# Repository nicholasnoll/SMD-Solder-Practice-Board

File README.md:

# SMD Solder Practice Board
 A 100x100mm board for SMD soldering practice

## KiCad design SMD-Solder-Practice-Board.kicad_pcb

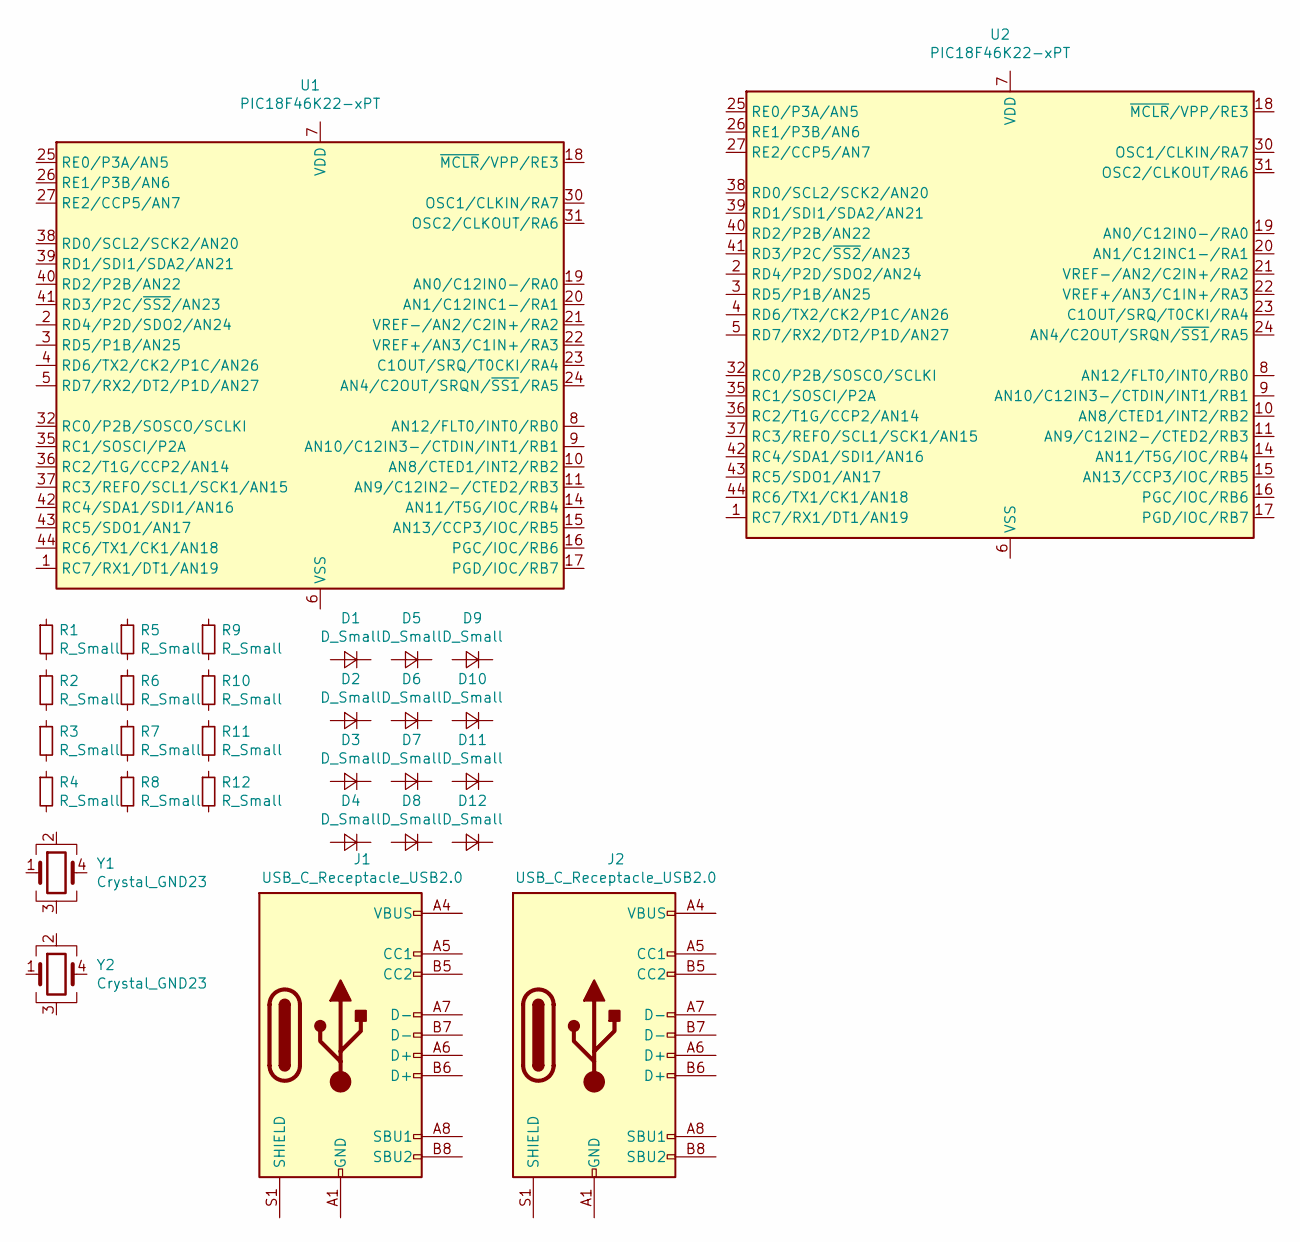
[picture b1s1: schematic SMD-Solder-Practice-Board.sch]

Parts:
D1, D2, D3, D4, D5, D6, D7, D8, D9, D10, D11, D12: D_Small; D_SOD-123
J1, J2: USB_C_Receptacle_USB2.0; USB_C_Receptacle_Palconn_UTC16-G
R1, R2, R3, R4, R5, R6, R7, R8, R9, R10, R11, R12: R_Small; R_0805_2012Metric
U1, U2: PIC18F46K22-xPT; TQFP-44_10x10mm_P0.8mm
Y1, Y2: Crystal_GND23; Crystal_SMD_3225-4Pin_3.2x2.5mm

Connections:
unnamed: J1.A1 (GND), J1.A12 (GND), J1.B1 (GND), J1.B12 (GND)
unnamed: J1.A4 (VBUS), J1.A9 (VBUS), J1.B4 (VBUS), J1.B9 (VBUS)
unnamed: J2.A1 (GND), J2.A12 (GND), J2.B1 (GND), J2.B12 (GND)
unnamed: J2.A4 (VBUS), J2.A9 (VBUS), J2.B4 (VBUS), J2.B9 (VBUS)
unnamed: U1.7 (VDD), U1.28 (VDD)
unnamed: U1.6 (VSS), U1.29 (VSS)
unnamed: U2.7 (VDD), U2.28 (VDD)
unnamed: U2.6 (VSS), U2.29 (VSS)

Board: 2 copper layers, 30 parts (0 on the bottom side), 8 nets, no tracks yet.

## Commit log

2022-12-24 Components and positioning
2022-12-24 gerbers
